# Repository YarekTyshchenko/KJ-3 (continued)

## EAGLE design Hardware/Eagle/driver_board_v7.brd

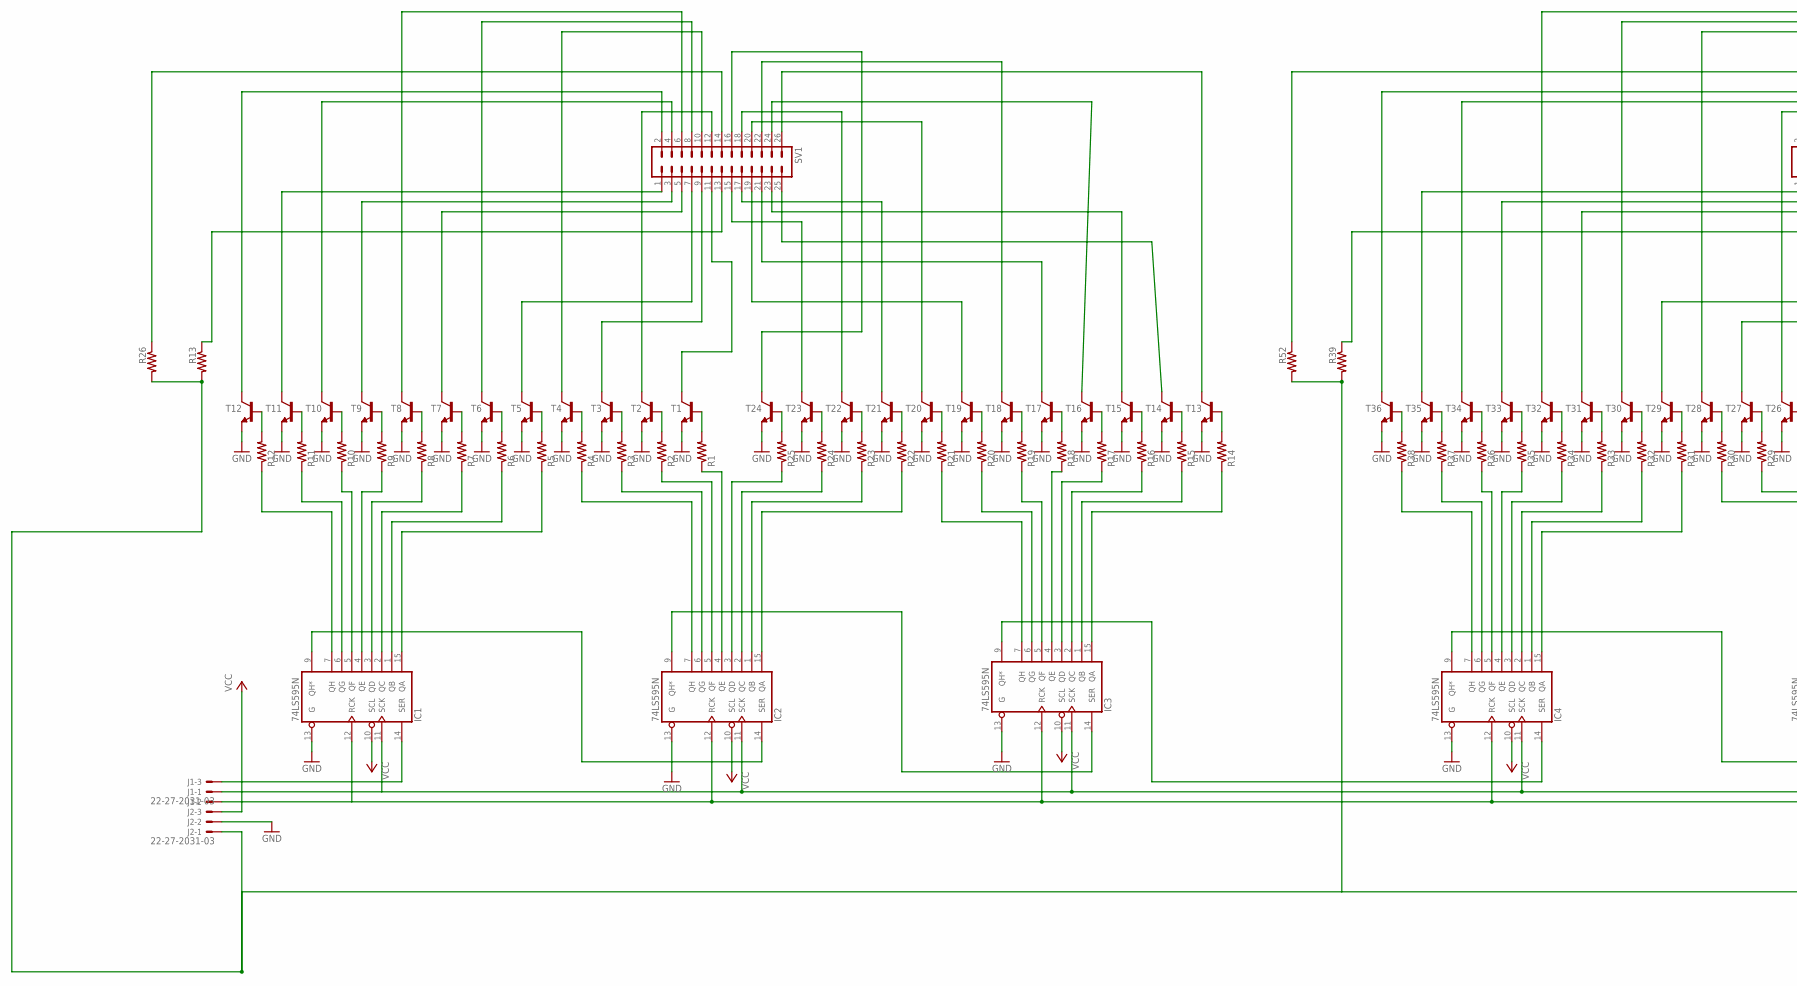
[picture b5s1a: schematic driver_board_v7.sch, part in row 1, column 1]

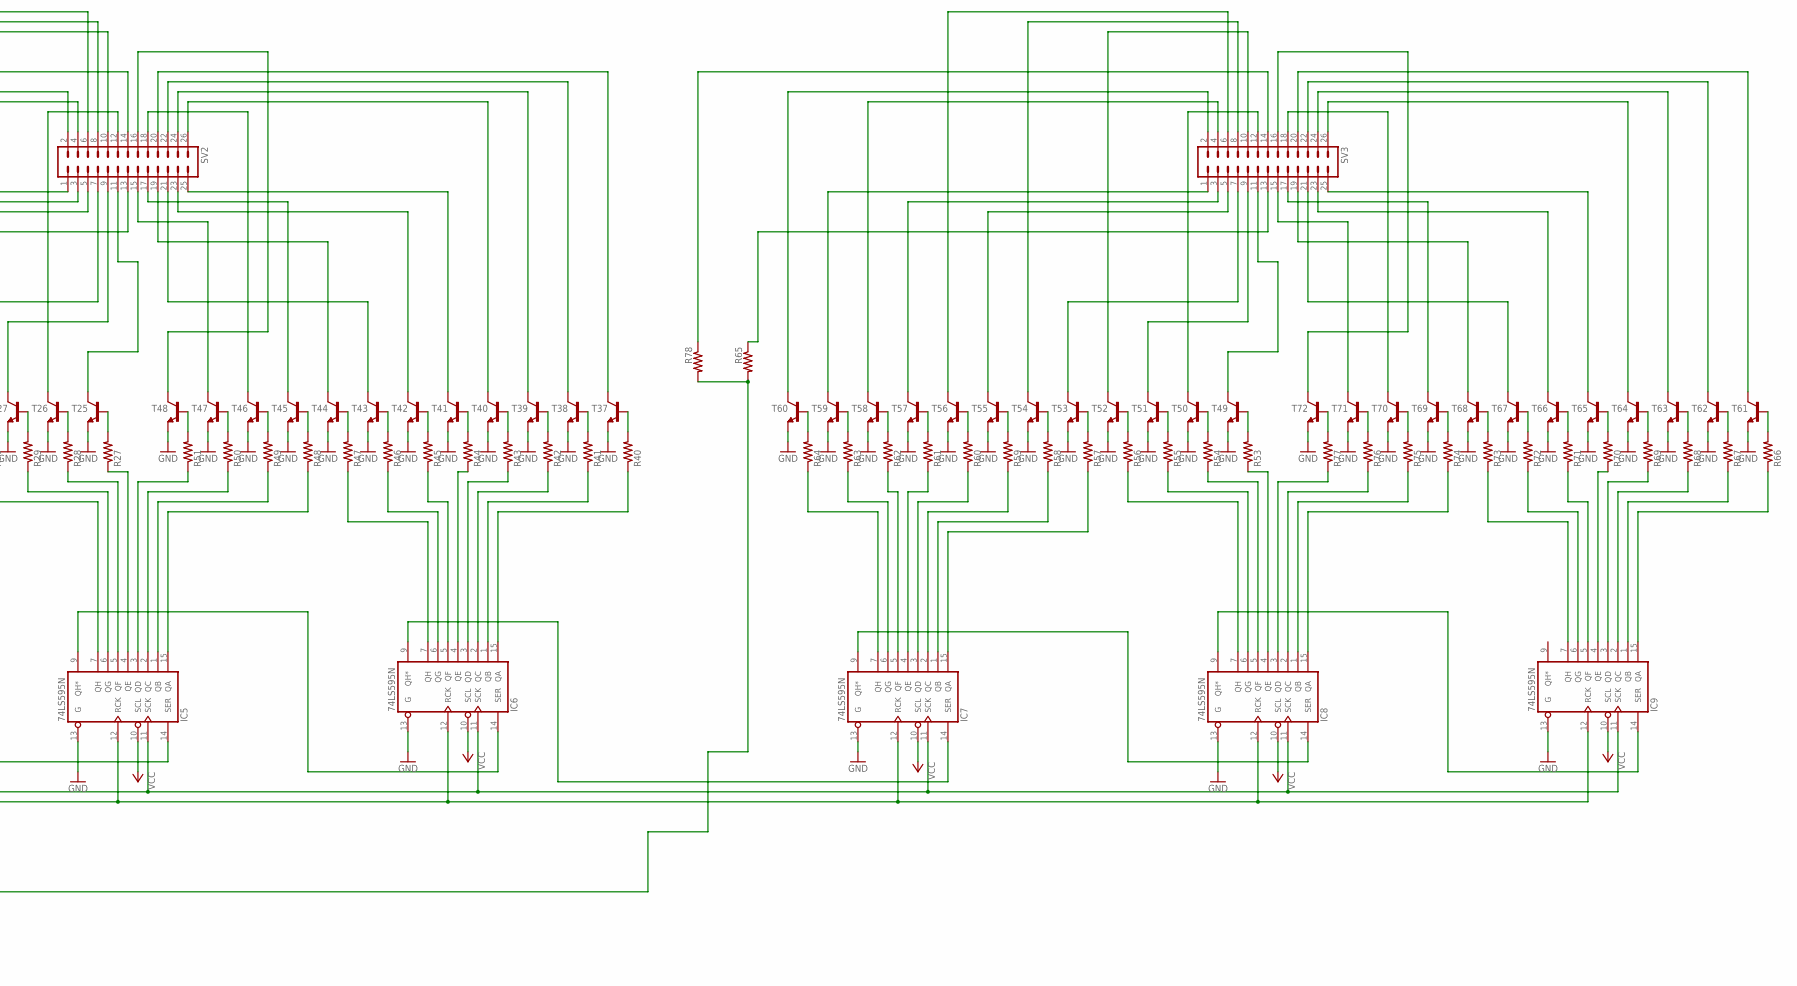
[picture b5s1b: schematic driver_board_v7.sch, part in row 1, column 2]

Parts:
IC1, IC2, IC3, IC4, IC5, IC6, IC7, IC8, IC9: 74LS595N; DIL16
J1, J2: 22-27-2031-03; 6410-03
R1, R2, R3, R4, R5, R6, R7, R8, R9, R10, R11, R12, R13, R14, R15, R16, R17, R18, R19, R20, R21, R22, R23, R24, R25, R26, R27, R28, R29, R30, R31, R32, R33, R34, R35, R36, R37, R38, R39, R40, R41, R42, R43, R44, R45, R46, R47, R48, R49, R50, R51, R52, R53, R54, R55, R56, R57, R58, R59, R60, R61, R62, R63, R64, R65, R66, R67, R68, R69, R70, R71, R72, R73, R74, R75, R76, R77, R78: R-US_0204/7; 0204/7
SV1, SV2, SV3: MA13-2
T1, T2, T3, T4, T5, T6, T7, T8, T9, T10, T11, T12, T13, T14, T15, T16, T17, T18, T19, T20, T21, T22, T23, T24, T25, T26, T27, T28, T29, T30, T31, T32, T33, T34, T35, T36, T37, T38, T39, T40, T41, T42, T43, T44, T45, T46, T47, T48, T49, T50, T51, T52, T53, T54, T55, T56, T57, T58, T59, T60, T61, T62, T63, T64, T65, T66, T67, T68, T69, T70, T71, T72: 29-NPN-TO92-EBC; TO92-EBC

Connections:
GND: IC1.8 (GND), IC1.13 (G), IC2.8 (GND), IC2.13 (G), IC3.8 (GND), IC3.13 (G), IC4.8 (GND), IC4.13 (G), IC5.8 (GND), IC5.13 (G), IC6.8 (GND), IC6.13 (G), IC7.8 (GND), IC7.13 (G), IC8.8 (GND), IC8.13 (G), IC9.8 (GND), IC9.13 (G), J2.2, T1.E, T2.E, T3.E, T4.E, T5.E, T6.E, T7.E, T8.E, T9.E, T10.E, T11.E, T12.E, T13.E, T14.E, T15.E, T16.E, T17.E, T18.E, T19.E, T20.E, T21.E, T22.E, T23.E, T24.E, T25.E, T26.E, T27.E, T28.E, T29.E, T30.E, T31.E, T32.E, T33.E, T34.E, T35.E, T36.E, T37.E, T38.E, T39.E, T40.E, T41.E, T42.E, T43.E, T44.E, T45.E, T46.E, T47.E, T48.E, T49.E, T50.E, T51.E, T52.E, T53.E, T54.E, T55.E, T56.E, T57.E, T58.E, T59.E, T60.E, T61.E, T62.E, T63.E, T64.E, T65.E, T66.E, T67.E, T68.E, T69.E, T70.E, T71.E, T72.E
HV: J2.1, R13.2, R26.2, R39.2, R52.2, R65.2, R78.2
unnamed: R12.2, T12.B
unnamed: R11.2, T11.B
unnamed: R10.2, T10.B
unnamed: R9.2, T9.B
unnamed: R8.2, T8.B
unnamed: R7.2, T7.B
unnamed: R6.2, T6.B
unnamed: R5.2, T5.B
unnamed: R4.2, T4.B
unnamed: R3.2, T3.B
unnamed: R2.2, T2.B
unnamed: R1.2, T1.B
unnamed: SV1.11, T1.C
unnamed: R38.2, T36.B
unnamed: R37.2, T35.B
unnamed: SV1.3, T9.C
unnamed: SV1.6, T8.C
unnamed: SV1.5, T7.C
unnamed: R36.2, T34.B
unnamed: SV1.12, T2.C
unnamed: SV1.9, T3.C
unnamed: SV1.8, T6.C
unnamed: SV1.7, T5.C
unnamed: SV1.10, T4.C
unnamed: R26.1, SV1.14
unnamed: R25.2, T24.B
unnamed: R24.2, T23.B
unnamed: R23.2, T22.B
unnamed: R22.2, T21.B
unnamed: R21.2, T20.B
unnamed: R20.2, T19.B
unnamed: R19.2, T18.B
unnamed: R18.2, T17.B
unnamed: R17.2, T16.B
unnamed: R16.2, T15.B
unnamed: R15.2, T14.B
unnamed: R14.2, T13.B
unnamed: SV1.16, T24.C
unnamed: SV1.15, T23.C
unnamed: SV1.18, T22.C
unnamed: SV1.17, T21.C
unnamed: SV1.20, T20.C
unnamed: SV1.19, T19.C
unnamed: SV1.26, T13.C
unnamed: SV1.25, T14.C
unnamed: SV1.23, T15.C
unnamed: SV1.22, T18.C
unnamed: SV1.21, T17.C
unnamed: SV1.24, T16.C
unnamed: R13.1, SV1.13
unnamed: IC1.9 (QH*), IC2.14 (SER)
unnamed: IC2.9 (QH*), IC3.14 (SER)
unnamed: IC3.9 (QH*), IC4.14 (SER)
unnamed: R35.2, T33.B
unnamed: SV1.2, T12.C
unnamed: SV1.1, T11.C
unnamed: SV1.4, T10.C
unnamed: R34.2, T32.B
unnamed: R33.2, T31.B
unnamed: R32.2, T30.B
unnamed: R31.2, T29.B
unnamed: R30.2, T28.B
unnamed: R29.2, T27.B
unnamed: R28.2, T26.B
unnamed: R27.2, T25.B
unnamed: SV2.3, T33.C
unnamed: SV2.6, T32.C
unnamed: SV2.5, T31.C
unnamed: SV2.12, T26.C
unnamed: SV2.9, T27.C
unnamed: IC1.7 (QH), R12.1
unnamed: IC1.6 (QG), R11.1
unnamed: IC1.5 (QF), R10.1
unnamed: IC1.4 (QE), R9.1
unnamed: IC1.3 (QD), R8.1
unnamed: IC1.2 (QC), R7.1
unnamed: IC1.1 (QB), R6.1
unnamed: IC1.15 (QA), R5.1
unnamed: SV2.8, T30.C
unnamed: IC2.7 (QH), R4.1
unnamed: IC2.6 (QG), R3.1
unnamed: IC2.5 (QF), R2.1
unnamed: IC2.4 (QE), R1.1
unnamed: IC2.3 (QD), R25.1
unnamed: IC2.2 (QC), R24.1
unnamed: IC2.1 (QB), R23.1
unnamed: IC2.15 (QA), R22.1
unnamed: IC3.7 (QH), R21.1
unnamed: IC3.6 (QG), R20.1
unnamed: IC3.5 (QF), R19.1
unnamed: IC3.4 (QE), R18.1
unnamed: IC3.3 (QD), R17.1
unnamed: IC3.2 (QC), R16.1
unnamed: IC3.1 (QB), R15.1
unnamed: IC3.15 (QA), R14.1
unnamed: SV2.7, T29.C
unnamed: SV2.10, T28.C
unnamed: R51.2, T48.B
unnamed: R50.2, T47.B
unnamed: R49.2, T46.B
unnamed: R48.2, T45.B
unnamed: R47.2, T44.B
unnamed: R46.2, T43.B
unnamed: R45.2, T42.B
unnamed: R44.2, T41.B
unnamed: R43.2, T40.B
unnamed: R42.2, T39.B
unnamed: R41.2, T38.B
unnamed: R40.2, T37.B
unnamed: SV2.16, T48.C
unnamed: SV2.15, T47.C
unnamed: SV2.18, T46.C
unnamed: SV2.17, T45.C
unnamed: SV2.19, T44.C
unnamed: SV2.21, T43.C
unnamed: SV2.20, T37.C
unnamed: SV2.22, T38.C
unnamed: SV2.24, T39.C
unnamed: SV2.23, T42.C
unnamed: SV2.25, T41.C
unnamed: SV2.26, T40.C
unnamed: IC4.7 (QH), R38.1
unnamed: IC4.6 (QG), R37.1
unnamed: IC4.5 (QF), R36.1
unnamed: IC4.4 (QE), R35.1
unnamed: IC4.3 (QD), R34.1
unnamed: IC4.2 (QC), R33.1
unnamed: IC4.1 (QB), R32.1
unnamed: IC4.15 (QA), R31.1
unnamed: IC5.7 (QH), R30.1
unnamed: IC5.6 (QG), R29.1
unnamed: IC5.5 (QF), R28.1
unnamed: IC5.4 (QE), R27.1
unnamed: IC5.3 (QD), R51.1
unnamed: IC5.2 (QC), R50.1
unnamed: IC5.1 (QB), R49.1
unnamed: IC5.15 (QA), R48.1
unnamed: IC6.7 (QH), R47.1
unnamed: IC6.6 (QG), R46.1
unnamed: IC6.5 (QF), R45.1
unnamed: IC6.4 (QE), R44.1
unnamed: IC6.3 (QD), R43.1
unnamed: IC6.2 (QC), R42.1
unnamed: IC6.1 (QB), R41.1
unnamed: IC6.15 (QA), R40.1
unnamed: IC4.9 (QH*), IC5.14 (SER)
unnamed: IC5.9 (QH*), IC6.14 (SER)
unnamed: IC6.9 (QH*), IC7.14 (SER)
unnamed: SV2.11, T25.C
unnamed: R52.1, SV2.14
unnamed: R39.1, SV2.13
unnamed: SV2.2, T36.C
unnamed: SV2.1, T35.C
unnamed: SV2.4, T34.C
unnamed: R64.2, T60.B
unnamed: R63.2, T59.B
unnamed: R62.2, T58.B
unnamed: R61.2, T57.B
unnamed: R60.2, T56.B
unnamed: R59.2, T55.B
unnamed: R58.2, T54.B
unnamed: R57.2, T53.B
unnamed: R56.2, T52.B
unnamed: R55.2, T51.B
unnamed: R54.2, T50.B
unnamed: R53.2, T49.B
unnamed: SV3.3, T57.C
unnamed: SV3.6, T56.C
unnamed: SV3.5, T55.C
unnamed: SV3.12, T50.C
unnamed: SV3.9, T51.C
unnamed: SV3.8, T54.C
unnamed: SV3.7, T53.C
unnamed: SV3.10, T52.C
unnamed: R77.2, T72.B
unnamed: R76.2, T71.B
unnamed: R75.2, T70.B
unnamed: R74.2, T69.B
unnamed: R73.2, T68.B
unnamed: R72.2, T67.B
unnamed: R71.2, T66.B
unnamed: R70.2, T65.B
unnamed: R69.2, T64.B
unnamed: R68.2, T63.B
unnamed: R67.2, T62.B
unnamed: R66.2, T61.B
unnamed: SV3.16, T72.C
unnamed: SV3.15, T71.C
unnamed: SV3.18, T70.C
unnamed: SV3.17, T69.C
unnamed: SV3.19, T68.C
unnamed: SV3.21, T67.C
unnamed: SV3.20, T61.C
unnamed: SV3.22, T62.C
unnamed: SV3.24, T63.C
unnamed: SV3.23, T66.C
unnamed: SV3.25, T65.C
unnamed: SV3.26, T64.C
unnamed: IC7.7 (QH), R64.1
unnamed: IC7.6 (QG), R63.1
unnamed: IC7.5 (QF), R62.1
unnamed: IC7.4 (QE), R61.1
unnamed: IC7.3 (QD), R60.1
unnamed: IC7.2 (QC), R59.1
unnamed: IC7.1 (QB), R58.1
unnamed: IC7.15 (QA), R57.1
unnamed: IC8.7 (QH), R56.1
unnamed: IC8.6 (QG), R55.1
unnamed: IC8.5 (QF), R54.1
unnamed: IC8.4 (QE), R53.1
unnamed: IC8.3 (QD), R77.1
unnamed: IC8.2 (QC), R76.1
unnamed: IC8.1 (QB), R75.1
unnamed: IC8.15 (QA), R74.1
unnamed: IC9.7 (QH), R73.1
unnamed: IC9.6 (QG), R72.1
unnamed: IC9.5 (QF), R71.1
unnamed: IC9.4 (QE), R70.1
unnamed: IC9.3 (QD), R69.1
unnamed: IC9.2 (QC), R68.1
unnamed: IC9.1 (QB), R67.1
unnamed: IC9.15 (QA), R66.1
unnamed: IC7.9 (QH*), IC8.14 (SER)
unnamed: IC8.9 (QH*), IC9.14 (SER)
unnamed: SV3.11, T49.C
unnamed: R78.1, SV3.14
unnamed: R65.1, SV3.13
unnamed: SV3.2, T60.C
unnamed: SV3.1, T59.C
unnamed: SV3.4, T58.C
RCK: IC1.12 (RCK), IC2.12 (RCK), IC3.12 (RCK), IC4.12 (RCK), IC5.12 (RCK), IC6.12 (RCK), IC7.12 (RCK), IC8.12 (RCK), IC9.12 (RCK), J1.2
SCK: IC1.11 (SCK), IC2.11 (SCK), IC3.11 (SCK), IC4.11 (SCK), IC5.11 (SCK), IC6.11 (SCK), IC7.11 (SCK), IC8.11 (SCK), IC9.11 (SCK), J1.1
SER: IC1.14 (SER), J1.3
VCC: IC1.10 (SCL), IC1.16 (VCC), IC2.10 (SCL), IC2.16 (VCC), IC3.10 (SCL), IC3.16 (VCC), IC4.10 (SCL), IC4.16 (VCC), IC5.10 (SCL), IC5.16 (VCC), IC6.10 (SCL), IC6.16 (VCC), IC7.10 (SCL), IC7.16 (VCC), IC8.10 (SCL), IC8.16 (VCC), IC9.10 (SCL), IC9.16 (VCC), J2.3

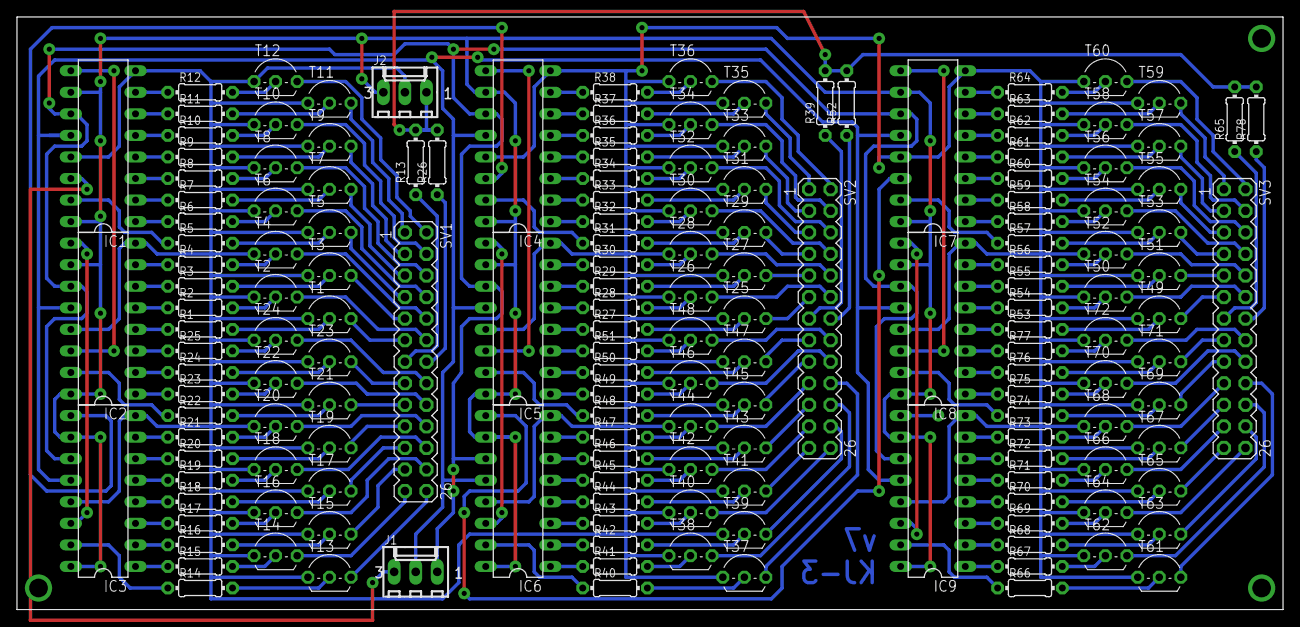
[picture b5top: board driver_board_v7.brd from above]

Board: 2 copper layers, 149.2 x 69.8 mm, 164 parts (0 on the bottom side), 236 nets.

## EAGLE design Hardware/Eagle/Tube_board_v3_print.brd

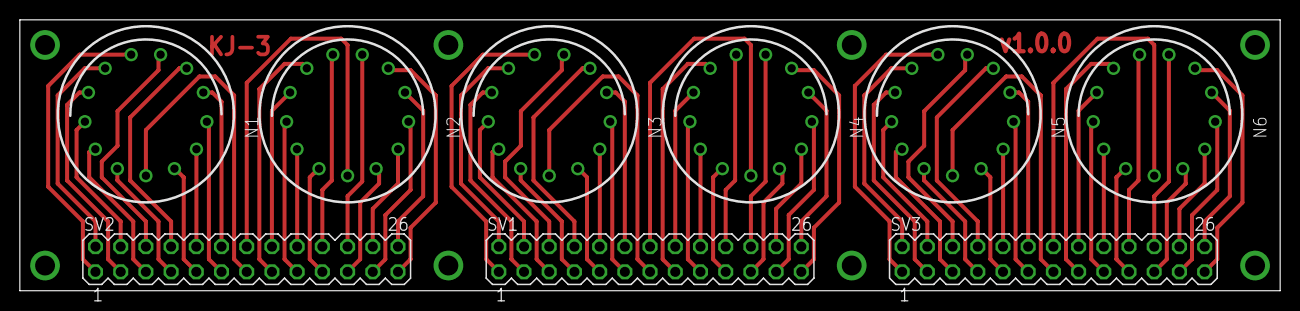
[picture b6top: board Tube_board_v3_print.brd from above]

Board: 2 copper layers, 127.0 x 27.3 mm, 9 parts (0 on the bottom side), 9 nets.

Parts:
N1, N2, N3, N4, N5, N6: IN-14
SV1, SV2, SV3: MA13-2

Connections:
unnamed: N1.A, SV2.13
unnamed: N2.A, SV2.14
unnamed: N1.0, N1.1, N1.2, N1.3, N1.4, N1.5, N1.6, N1.7, N1.8, N1.9, N1.LHDP, N1.RHDP, N2.0, N2.1, N2.2, N2.3, N2.4, N2.5, N2.6, N2.7, N2.8, N2.9, N2.LHDP, N2.RHDP, SV2.1, SV2.2, SV2.3, SV2.4, SV2.5, SV2.6, SV2.7, SV2.8, SV2.9, SV2.10, SV2.11, SV2.12, SV2.15, SV2.16, SV2.17, SV2.18, SV2.19, SV2.20, SV2.21, SV2.22, SV2.23, SV2.24, SV2.25, SV2.26
unnamed: N3.A, SV1.13
unnamed: N4.A, SV1.14
unnamed: N3.0, N3.1, N3.2, N3.3, N3.4, N3.5, N3.6, N3.7, N3.8, N3.9, N3.LHDP, N3.RHDP, N4.0, N4.1, N4.2, N4.3, N4.4, N4.5, N4.6, N4.7, N4.8, N4.9, N4.LHDP, N4.RHDP, SV1.1, SV1.2, SV1.3, SV1.4, SV1.5, SV1.6, SV1.7, SV1.8, SV1.9, SV1.10, SV1.11, SV1.12, SV1.15, SV1.16, SV1.17, SV1.18, SV1.19, SV1.20, SV1.21, SV1.22, SV1.23, SV1.24, SV1.25, SV1.26
unnamed: N5.A, SV3.13
unnamed: N6.A, SV3.14
unnamed: N5.0, N5.1, N5.2, N5.3, N5.4, N5.5, N5.6, N5.7, N5.8, N5.9, N5.LHDP, N5.RHDP, N6.0, N6.1, N6.2, N6.3, N6.4, N6.5, N6.6, N6.7, N6.8, N6.9, N6.LHDP, N6.RHDP, SV3.1, SV3.2, SV3.3, SV3.4, SV3.5, SV3.6, SV3.7, SV3.8, SV3.9, SV3.10, SV3.11, SV3.12, SV3.15, SV3.16, SV3.17, SV3.18, SV3.19, SV3.20, SV3.21, SV3.22, SV3.23, SV3.24, SV3.25, SV3.26

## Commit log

2014-07-07 Add Eagle board files
2014-07-14 Implemented NTP and refactored Tube logic into its own class
2014-07-23 Tweaked Software
    Swapped tube pins for easier PCB routing. Uncommented bunch of debug
    stuff
2014-07-23 Correct Tube pins, and comment out Ethernet init
2014-07-28 Add USBTintISP board
    Also cleaned up some old pcb designs
2014-10-30 Added steps to work with Arduino Micro as ISP
2014-10-30 Add in Time and Ethercard libraries to make building the project easier
2014-10-30 Implement TimeZone library for UK time
2014-10-30 Add Timezone library
2014-10-30 WIP
    A bunch of changes to bring it back into operation. Note that the
    Ethernet Chip pin is 10.
2014-10-31 Cleanup some of the code
2014-10-31 Reindent the source code
2014-10-31 Refactor Ntp code into a file
2014-10-31 Add degauss
2014-10-31 Math fail
2014-10-31 Give ntp a bit of a breather before initiating update
2014-11-07 Update display and flash dots, WIP
2014-11-07 Make dots flash (Commented out)
2014-11-07 Add a UDP interface to turn off the tubes
    This should help with uploading code without manually disabling the tubes
2014-11-07 Some more WIP with UDP
2014-11-08 Disable tubes on UDP access
2014-11-08 More experimentation with UDP
2014-11-08 Implement a clear bootup sequence
2014-12-09 Add real NTP server and improve the timeout
2014-12-09 Clean up some old code. Removed: Updates per second and displayNumber
2014-12-24 Bug with passing function by reference
2014-12-25 More experimental WIP
2014-12-26 More WIP with Json stuff
2014-12-26 Move ethercard library into correct folder
2014-12-26 Fix UDP functions in NtpClient class
2014-12-26 Implement JSON stuff + frame rate
2014-12-26 Moved Time and Timezone libraries into the correct folder
2014-12-27 Implement timer mode
2015-03-19 Update modes so they work properly
